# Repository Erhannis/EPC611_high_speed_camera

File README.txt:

NOT YET FINISHED.
Testing yielded mixed results.

Turn a EPC611 ToF 8x8 image sensor into a 4000fps high speed greyscale camera.
Expected parts cost...like $25 probably.

I did some testing on some JLCPCB boards - I did get some high speed results (I forget how fast) -
1. I had some difficulty getting the data off the board into the computer fast enough and accurately
2. The FOV was *very* small, which made it hard to test right, hard to tell what I was looking at, etc.
3. The picture seemed kinda...splotchy?  Like there were patches that were stained bright or dark or st, moreso toward the edges.

Released MIT license.  Derived from the EPC611 spec sheet, not sure to what extent that affects this?

-Erhannis

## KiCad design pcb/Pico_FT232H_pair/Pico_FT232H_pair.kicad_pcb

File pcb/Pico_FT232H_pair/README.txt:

This was sorta cobbled together from:

datasheets,

https://github.com/gregdavill/advent-calendar-of-circuits-2020/tree/main/jtag-programmer , licensed CERN-OHL-P-2.0,

https://github.com/technoblogy/minimal-rp2040-board ,
http://www.technoblogy.com/show?3U75 ,
which have no license I can see,

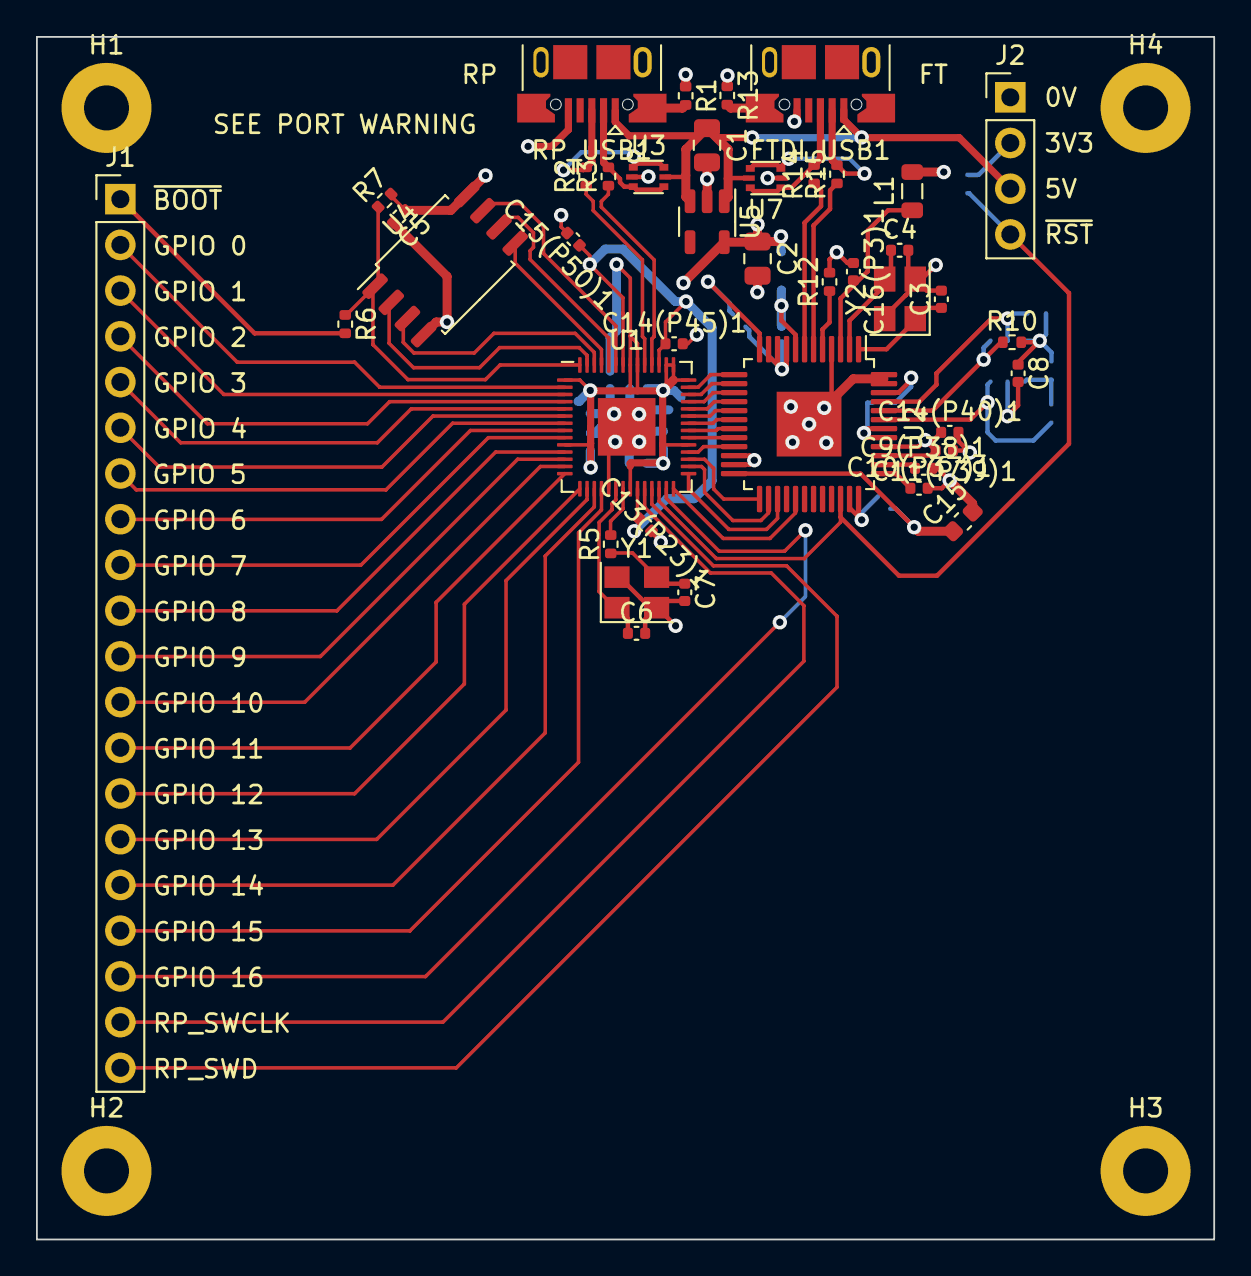
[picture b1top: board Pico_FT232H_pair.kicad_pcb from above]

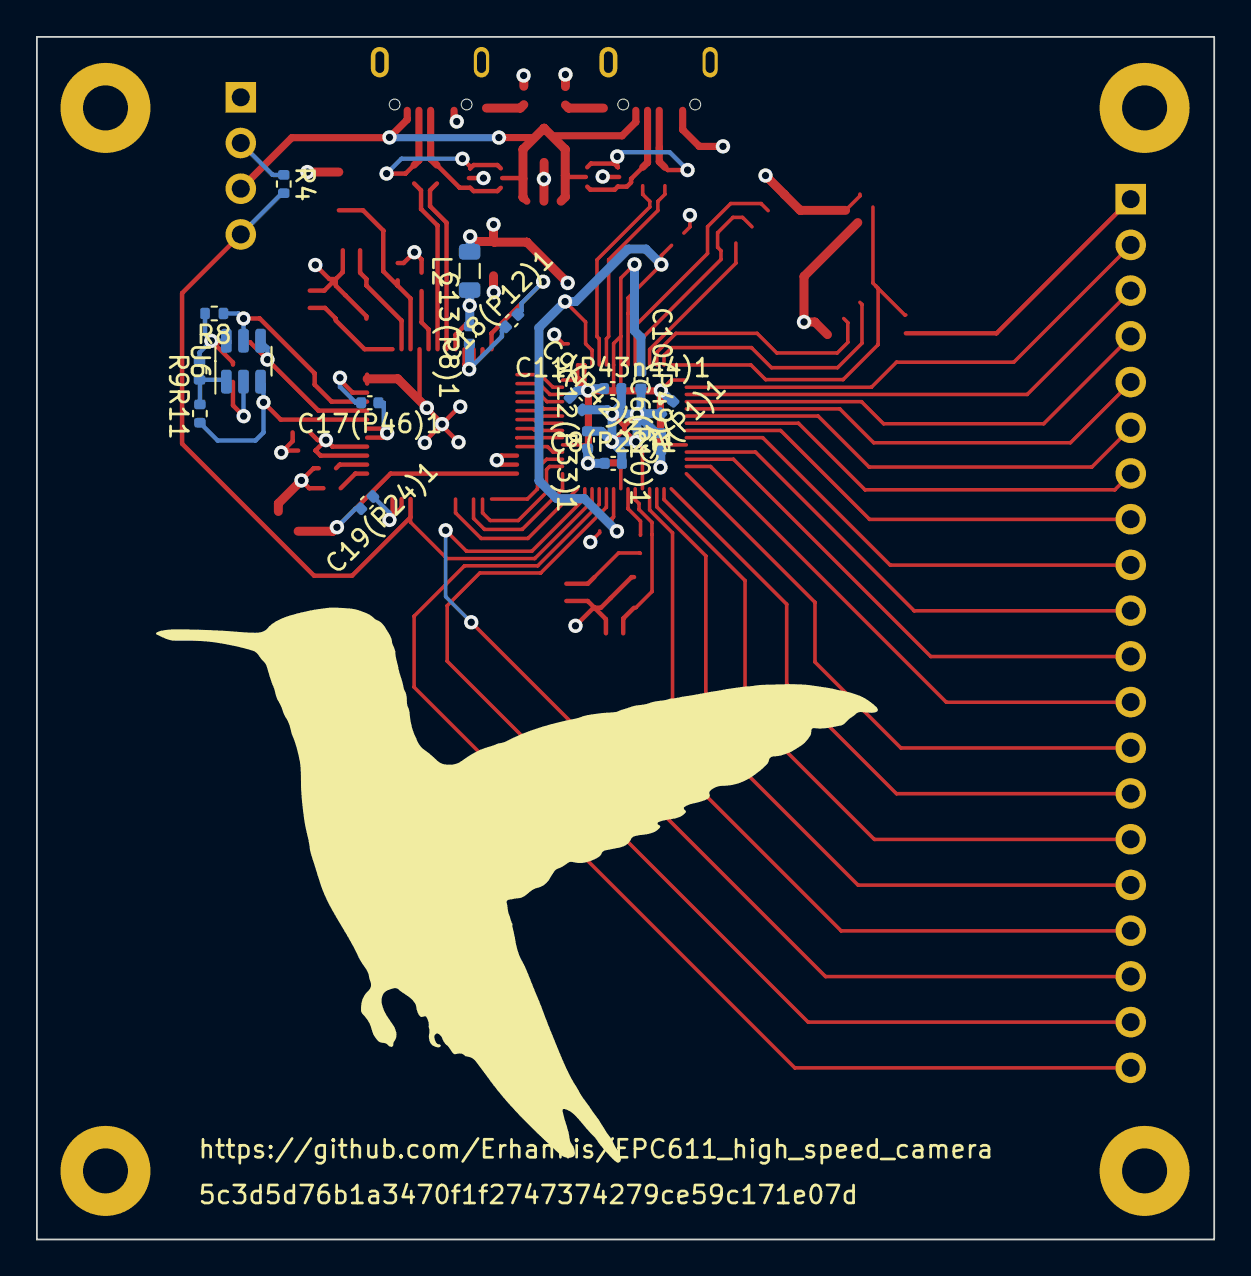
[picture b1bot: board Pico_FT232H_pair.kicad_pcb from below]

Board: 4 copper layers, 65.4 x 66.8 mm, 62 parts (17 on the bottom side), 68 nets.

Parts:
C1, C2: 10uF; C_0805_2012Metric
C3, C4, C6, C7: 35pF; C_0402_1005Metric
C5, C6(P10)1, C7(P1)1, C8, C8(P22)1, C9(P42)1, C10(P49)1, C12(P33)1, C13(P23)1, C15(P50)1: 100nF; C_0402_1005Metric
C9(P38)1, C10(P37)1, C11(P39)1, C14(P40)1: 100n; C_0402_1005Metric
C11(P43n44)1, C14(P45)1: 1uF; C_0402_1005Metric
C13(P8)1, C16(P3)1, C17(P46)1, C18(P12)1, C19(P24)1: 4u7; C_0402_1005Metric
C15: 4u7; C_0603_1608Metric
FTDI_USB1: USB_B_Micro; USB_Micro-B_XKB_U254-051T-4BH83-F1S
H1, H2, H3, H4: MountingHole_Pad; MountingHole_2.5mm_Pad
J1: Conn_01x20_Pin; PinHeader_1x20_P2.54mm_Vertical
J2: Conn_01x04_Pin; PinHeader_1x04_P2.54mm_Vertical
L1, L2: 600R/0.5A; L_0805_2012Metric
R1, R13: 1M; R_0402_1005Metric
R2, R3, R14, R15: 27; R_0402_1005Metric
R4, R7, R8, R9, R10: 10K; R_0402_1005Metric
R5: 1K; R_0402_1005Metric
R6: 1k; R_0402_1005Metric
R11: 2K; R_0402_1005Metric
R12: 12k; R_0402_1005Metric
RP_USB1: USB_B_Micro; USB_Micro-B_XKB_U254-051T-4BH83-F1S
U1: RP2040; QFN-56-1EP_7x7mm_P0.4mm_EP3.2x3.2mm
U2: FT232H; LQFP-48-1EP_7x7mm_P0.5mm_EP3.6x3.6mm
U3, U7: USBLC6-2P6; SOT-666
U4: W25Q128JVS; SOIC-8_5.23x5.23mm_P1.27mm
U5: AP2112K-3.3; SOT-23-5
U6: 93LCxxB; SOT-23-6
Y1, Y2: 12MHz; Crystal_SMD_3225-4Pin_3.2x2.5mm

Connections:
+1V2: C13(P23)1.1, C14(P45)1.1, C15(P50)1.1, U1.23 (DVDD), U1.45 (VREG_VOUT), U1.50 (DVDD)
+3V3: C2.1, C5.1, C6(P10)1.1, C7(P1)1.1, C8.1, C8(P22)1.1, C9(P42)1.1, C10(P49)1.1, C11(P39)1.2, C11(P43n44)1.1, C12(P33)1.1, C14(P40)1.1, C15.1, C17(P46)1.2, C18(P12)1.2, C19(P24)1.2, J2.2, L1.2, L2.2, R4.1, R7.2, R8.2, R9.2, R10.2, U1.1 (IOVDD), U1.10 (IOVDD), U1.22 (IOVDD), U1.33 (IOVDD), U1.42 (IOVDD), U1.43 (ADC_AVDD), U1.44 (VREG_IN), U1.48 (USB_VDD), U1.49 (IOVDD), U2.12 (VCCIO), U2.24 (VCCIO), U2.39 (VCCD), U2.40 (VREGIN), U2.46 (VCCIO), U4.8 (VCC), U5.5 (VOUT), U6.6 (VCC)
+5V: C1.1, FTDI_USB1.1 (VBUS), J2.3, RP_USB1.1 (VBUS), U3.5 (VBUS), U5.1 (VIN), U5.3 (EN), U7.5 (VBUS)
/EEPROM/CLK: R10.1, U2.44 (EECLK), U6.4 (CLK)
/EEPROM/CS#: R8.1, U2.45 (EECS), U6.5 (CS)
/EEPROM/DATA: R11.1, U2.43 (EEDATA), U6.3 (DI)
/FT_UD+: R14.1, U2.7 (DP)
/FT_UD-: R15.1, U2.6 (DM)
/QSPI_CS: R6.1, R7.1, U1.56 (QSPI_SS), U4.1 (~CS)
/QSPI_DATA[0]: U1.53 (QSPI_SD0), U4.5 (DI(IO0))
/QSPI_DATA[1]: U1.55 (QSPI_SD1), U4.2 (DO(IO1))
/QSPI_DATA[2]: U1.54 (QSPI_SD2), U4.3 (IO2)
/QSPI_DATA[3]: U1.51 (QSPI_SD3), U4.7 (IO3)
/QSPI_SCK: U1.52 (QSPI_SCLK), U4.6 (CLK)
/RP_SWCLK: J1.19, U1.24 (SWCLK)
/RP_SWD: J1.20, U1.25 (SWD)
/RP_UD+: R2.1, U1.47 (USB_DP)
/RP_UD-: R3.1, U1.46 (USB_DM)
/USB_BOOT: J1.1, R6.2
/~RESET: J2.4, R4.2, U1.26 (RUN), U2.34 (~RESET)
GND: C1.2, C2.2, C3.2, C4.2, C5.2, C6.2, C6(P10)1.2, C7.2, C7(P1)1.2, C8.2, C8(P22)1.2, C9(P38)1.2, C9(P42)1.2, C10(P37)1.2, C10(P49)1.2, C11(P39)1.1, C11(P43n44)1.2, C12(P33)1.2, C13(P8)1.1, C13(P23)1.2, C14(P40)1.2, C14(P45)1.2, C15.2, C15(P50)1.2, C16(P3)1.1, C17(P46)1.1, C18(P12)1.1, C19(P24)1.1, FTDI_USB1.5 (GND), H1.1, H2.1, H3.1, H4.1, J2.1, R1.1, R12.2, R13.1, RP_USB1.5 (GND), U1.19 (TESTEN), U1.57 (GND), U2.4 (AGND), U2.9 (AGND), U2.10 (GND), U2.11 (GND), U2.22 (GND), U2.23 (GND), U2.35 (GND), U2.36 (GND), U2.41 (AGND), U2.42 (TEST), U2.47 (GND), U2.48 (GND), U2.49, U3.2 (GND), U4.4 (GND), U5.2 (GND), U6.2 (GND), U7.2 (GND), Y1.2, Y1.4, Y2.2, Y2.4
unnamed: C7.1, R5.1, Y1.3
unnamed: FTDI_USB1.3 (D+), R14.2, U7.1 (I/O1), U7.6 (I/O1)
unnamed: FTDI_USB1.2 (D-), R15.2, U7.3 (I/O2), U7.4 (I/O2)
unnamed: FTDI_USB1.6 (Shield), R13.2
unnamed: J1.2, U1.2 (GPIO0)
unnamed: J1.3, U1.3 (GPIO1)
unnamed: J1.4, U1.4 (GPIO2)
unnamed: J1.5, U1.5 (GPIO3)
unnamed: J1.6, U1.6 (GPIO4)
unnamed: J1.7, U1.7 (GPIO5)
unnamed: J1.8, U1.8 (GPIO6)
unnamed: J1.9, U1.9 (GPIO7)
unnamed: J1.10, U1.11 (GPIO8)
unnamed: J1.11, U1.12 (GPIO9)
unnamed: J1.12, U1.13 (GPIO10)
unnamed: J1.13, U1.14 (GPIO11)
unnamed: J1.14, U1.15 (GPIO12)
unnamed: J1.15, U1.16 (GPIO13)
unnamed: J1.16, U1.17 (GPIO14)
unnamed: J1.17, U1.18 (GPIO15)
unnamed: J1.18, U1.27 (GPIO16)
unnamed: R2.2, RP_USB1.3 (D+), U3.1 (I/O1), U3.6 (I/O1)
unnamed: R3.2, RP_USB1.2 (D-), U3.3 (I/O2), U3.4 (I/O2)
unnamed: R1.2, RP_USB1.6 (Shield)
unnamed: U1.28 (GPIO17), U2.29 (ACBUS5)
unnamed: U1.29 (GPIO18), U2.27 (ACBUS3)
unnamed: U1.30 (GPIO19), U2.26 (ACBUS2)
unnamed: U1.31 (GPIO20), U2.25 (ACBUS1)
unnamed: U1.32 (GPIO21), U2.21 (ACBUS0)
unnamed: U1.34 (GPIO22), U2.20 (ADBUS7)
unnamed: U1.35 (GPIO23), U2.19 (ADBUS6)
unnamed: U1.36 (GPIO24), U2.18 (ADBUS5)
unnamed: U1.37 (GPIO25), U2.17 (ADBUS4)
unnamed: U1.38 (GPIO26_ADC0), U2.16 (ADBUS3)
unnamed: U1.39 (GPIO27_ADC1), U2.15 (ADBUS2)
unnamed: U1.40 (GPIO28_ADC2), U2.14 (ADBUS1)
unnamed: U1.41 (GPIO29_ADC3), U2.13 (ADBUS0)
unnamed: C6.1, U1.20 (XIN), Y1.1
unnamed: R5.2, U1.21 (XOUT)
unnamed: R12.1, U2.5 (REF)
unnamed: C10(P37)1.1, U2.37 (VCCA)
unnamed: C9(P38)1.1, U2.38 (VCCCORE)
unnamed: C16(P3)1.2, L1.1, U2.3 (VPHY)
unnamed: C13(P8)1.2, L2.1, U2.8 (VPLL)
unnamed: C3.1, U2.1 (XCSI), Y2.1
unnamed: C4.1, U2.2 (XCSO), Y2.3
unnamed: R9.1, R11.2, U6.1 (DO)

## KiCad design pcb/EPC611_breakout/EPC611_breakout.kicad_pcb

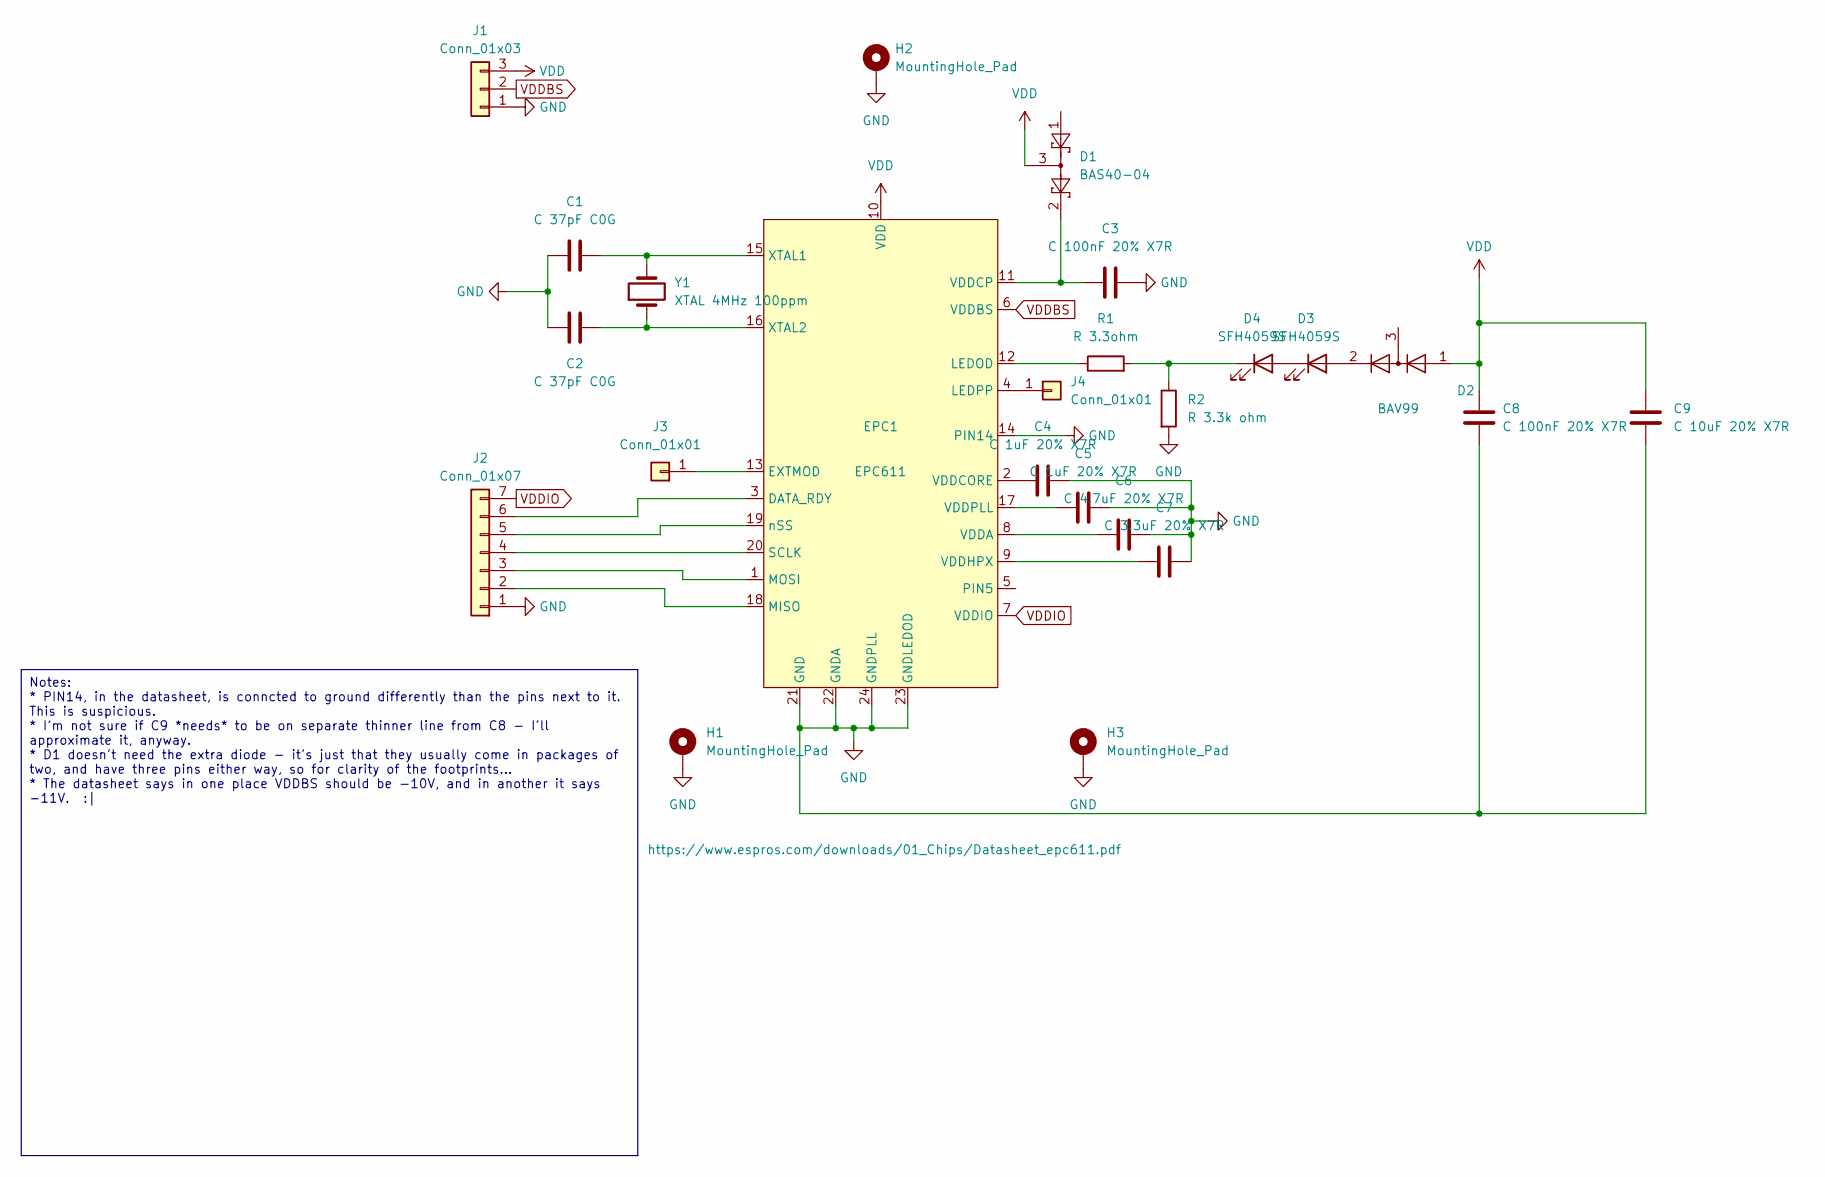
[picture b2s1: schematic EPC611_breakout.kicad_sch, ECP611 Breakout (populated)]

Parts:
C1, C2: C 37pF C0G; C_0402_1005Metric; LCSC C415391
C3, C8: C 100nF 20% X7R; C_0805_2012Metric; LCSC C360619
C4, C5: C 1uF 20% X7R; C_0805_2012Metric; LCSC C376929
C6: C 4.7uF 20% X7R; C_0805_2012Metric; LCSC C337439
C7: C 3.3uF 20% X7R; C_0805_2012Metric; LCSC C361184
C9: C 10uF 20% X7R; C_1206_3216Metric; LCSC C303950
D1: BAS40-04; SOT-23; LCSC C5184421
D2: BAV99; SOT-23; LCSC C68983
D3, D4: SFH4059S; LED_1206_3216Metric
EPC1: EPC611; EPC611_CSP-24
H1, H2, H3: MountingHole_Pad; MountingHole_2.5mm_Pad
J1: Conn_01x03; PinHeader_1x03_P2.54mm_Vertical; LCSC C49257
J2: Conn_01x07; PinHeader_1x07_P2.54mm_Vertical; LCSC C2894930
J3, J4: Conn_01x01; PinHeader_1x01_P2.54mm_Vertical; LCSC C81276
R1: R 3.3ohm; R_1206_3216Metric; LCSC C2930397
R2: R 3.3k ohm; R_0603_1608Metric; LCSC C22978
Y1: XTAL 4MHz 100ppm; Crystal_SMD_HC49-SD; LCSC C13774

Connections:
GND: C1.1, C2.2, C3.2, C4.2, C5.2, C6.2, C7.2, C8.2, C9.2, EPC1.14 (PIN14), EPC1.21 (GND), EPC1.22 (GNDA), EPC1.23 (GNDLEDOD), EPC1.24 (GNDPLL), H1.1, H2.1, H3.1, J1.1, J2.1, R2.2
unnamed: D2.2 (A), D3.2 (A)
unnamed: D3.1 (K), D4.2 (A)
unnamed: D4.1 (K), R1.2, R2.1
unnamed: EPC1.3 (DATA_RDY), J2.6
unnamed: EPC1.13 (EXTMOD), J3.1
unnamed: EPC1.12 (LEDOD), R1.1
unnamed: EPC1.4 (LEDPP), J4.1
unnamed: EPC1.18 (MISO), J2.2
unnamed: EPC1.1 (MOSI), J2.3
unnamed: EPC1.20 (SCLK), J2.4
unnamed: C6.1, EPC1.8 (VDDA)
unnamed: C4.1, EPC1.2 (VDDCORE)
unnamed: C3.1, D1.2, EPC1.11 (VDDCP)
unnamed: C7.1, EPC1.9 (VDDHPX)
unnamed: C5.1, EPC1.17 (VDDPLL)
unnamed: C1.2, EPC1.15 (XTAL1), Y1.2
unnamed: C2.1, EPC1.16 (XTAL2), Y1.1
unnamed: EPC1.19 (nSS), J2.5
VDD: C8.1, C9.1, D1.3, D2.1 (K), EPC1.10 (VDD), J1.3
VDDBS: EPC1.6 (VDDBS), J1.2
VDDIO: EPC1.7 (VDDIO), J2.7

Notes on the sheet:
Notes: * PIN14, in the datasheet, is conncted to ground differently than the pins next to it. This is suspicious. * I'm not sure if C9 *needs* to be on separate thinner line from C8 - I'll approximate it, anyway. * D1 doesn't need the extra diode - it's just that they usually come in packages of tw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

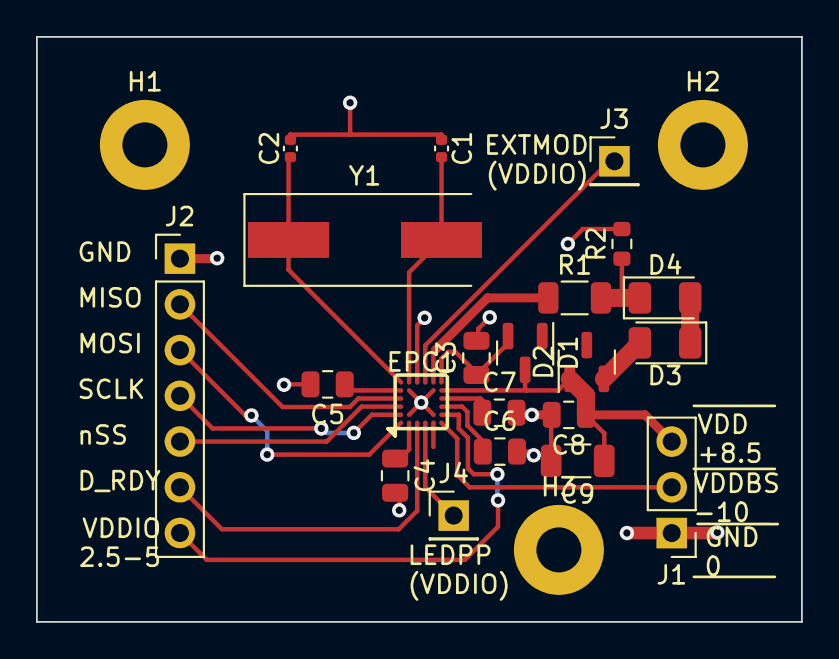
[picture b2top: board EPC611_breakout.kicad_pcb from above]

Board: 2 copper layers, 42.5 x 32.5 mm, 24 parts (0 on the bottom side), 22 nets.

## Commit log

2023-07-07 Initial commit. Trying to make a low-res high-speed camera, like 4000fps. I think I've transcribed the example schematic from the epc611 datasheet. Still need to check it over, add footprints, make l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
2023-07-07 Checked, fixed, tweaked schematic
2023-07-07 More edits
2023-07-07 add notes
2023-07-07 Added readme
2023-07-07 gitignore
2023-07-08 Found JLCPCB codes and matching footprints for all the bits, except the leds and the main chip
2023-07-08 Man for a minute I thought I was going to have to replace all my metric footprints with imperial ones, and then realized they'd been imperial the whole time
2023-07-08 Holy cow, I'm just now starting to absorb how small this chip actually is; I'm getting kinda worried. Chip footprint is halfway done
2023-07-08 tweaks
2023-07-08 Ok, I think this footprint may be right
2023-07-08 Oh right, link the symbol and the footprint together.
2023-07-08 Working on pcb
2023-07-08 Ok...it maaay be correct and done, now?
2023-07-08 Added hash
2023-07-08 ...Ffffine, I'll add an image for pretty.
2023-07-08 AND added mount holes
2023-07-08 hash
2023-07-08 Psh, of course I forgot some labels. Oh well, I'm not going through the upload process again for that.
2023-07-29 I think I made some labeling tweaks to the pcb. Also moved in initial code to talk to the chip. It's working! The talking bit. Haven't quite gotten to image capture yet.
2023-07-29 Hooray! We're getting image data, and it responds to light!
2023-07-29 AHAHA! It works! I focused my phone flashlight at it through a tiny lens, and it showed a corresponding pattern in the readout!
2023-07-29 Man, that bit unpacking was dumb
2023-07-29 Ok, the high-depth data now works, and at the cost of only like 15 microseconds a frame
2023-08-04 Host code, currently pulls artificially clocked 7 bits, poc
2023-08-05 Added a bunch of code for analysis. Couldn't nail down the glitches; trying CPU FIFO mode next.
2023-08-08 Half of the way through the schematic
2023-08-08 Labeled the caps by pin. I think I'm done with the RP2040 part of the schematic.
2023-08-09 Almost done with the schematic, just need to rejigger the USB stuff
2023-08-09 Ok; I think maybe, just maybe, I'm actually done with the schematic.
2023-08-09 Fixed some footprints, remembered the headers
2023-08-09 Er, right. Ok, I think I've got all the footprints lined up, and now it's on to mucking around with the PCB layout.
2023-08-09 Checkpoint; partway through the pcb
2023-08-09 I am probably royally bunging things up
2023-08-09 Checkpoint. I was hoping to finish this before the new day started....
2023-08-09 Work continues. Realized the inductors were probably the wrong ones, and attached wrong.
2023-08-09 Checkpoint
2023-08-09 Checkpoint. Nearly done?
2023-08-09 Added warning
2023-08-09 Fixed disconnected 1.2V. Working on DRC.
2023-08-09 Ok, all the DRC checks out
2023-08-09 Added mounting holes
2023-08-09 Added bird image
2023-08-09 Hash, url
2023-08-10 So ok, get this. A crystal says "20pF", right? So you use 20pF capacitors to match. WRONG! Apparently you use like, 2*20pF-3pF capactitors. Facepalm.
2023-08-10 Updated xtal caps. May not be exactly right, still. The device still WORKED with caps half as big as they supposedly should be, though, so....
2023-08-10 JLCPCB doesn't like component names containing commas, apparently.
2023-08-10 Ok, apparently jlcpcb doens't like commas or pipes in component names, and just skips them. Also, apparently I had the wrong footprint for one of the types of cap.
2023-08-12 I replaced all the weird imported symbols with built in ones
2023-08-18 Tweaked the shield grounding pins slightly and the edge of the board etc.
2023-08-19 Added a 3dp lens mount for the epc611 breakout. Also working on a display program.
2023-08-21 So I think I got up to 700 fps! I think I've reached the limit of the ESP32's usb serial connection, though. ...So it's good news that my pico/ftdi boards just arrived and apparently they work!! Init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
2023-08-21 Aha! Success! Mostly. Apparently that one set_bits line was bad. We're down to ~1/700 error rate, I can probably accept that.
2023-08-21 Seems like the error rate increases as the rate increases
2023-08-21 Switched back to test my skywired setup. Once I remembered to unreverse the bits, got basically the same result as on the board.
2023-08-22 Shows indices of skips, now. Looks like I've got the error rate down to less than one in a million, so...good. Even if 6.8MB/s is slower than I can accept in the long run.
2023-08-22 Ehh, maybe should limit skip indices shown
2023-08-22 Reverse asc/desc order
2023-08-24 Working on a display
2023-08-24 Ok, I've got it displaying SOMETHING, now
2023-08-26 Added counts, switched to binary, for tests
2023-08-27 Ok, I'm seeing images that correlate to things in front of the lens. There's some noise and/or corruption, though.
2023-08-31 Trying to fix it so I can see in realtime, for testing
2023-09-01 Man, I keep getting this wrong. Needs more thought.
2023-09-01 Sorta gave up on the regularized fps thing, because I don't actually need it right now. I managed to get a plausibly focused image, by putting a perforated tin foil cover over paper over a flashlight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
2023-09-01 Added mode toggles. Managed to capture the motion of a handheld fan blade. This thing has SUCH a small FOV, though, it's really hard to capture much, at least on the desk
2023-09-02 Forgot to commit, apparently. Trying to tune stuff. It's now becoming a problem that I'm not getting a smooth frame rate, so I guess it's time to fix it.
2023-09-02 Another failure
2023-09-02 Ok, I think I finally got the FPS thing working, though it feels like it has more latency than it had
2023-09-02 Tweak
2023-09-06 Added a dummy mode, and I think fixed some other things. Also tweaked the s-mount, though I guess the pcb'll change before that really matters.
2023-10-17 WARNING I just figured out that 7cbdafaa36fdf98c36a111cf436483cad7b3c00f broke stuff; I didn't properly reconnect at least the RP flash chip. There COULD be other things I broke. But anyway, this com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
2023-10-17 Ok, I think maybe I've fixed it?
2025-10-08 Update README.txt with remembered results
